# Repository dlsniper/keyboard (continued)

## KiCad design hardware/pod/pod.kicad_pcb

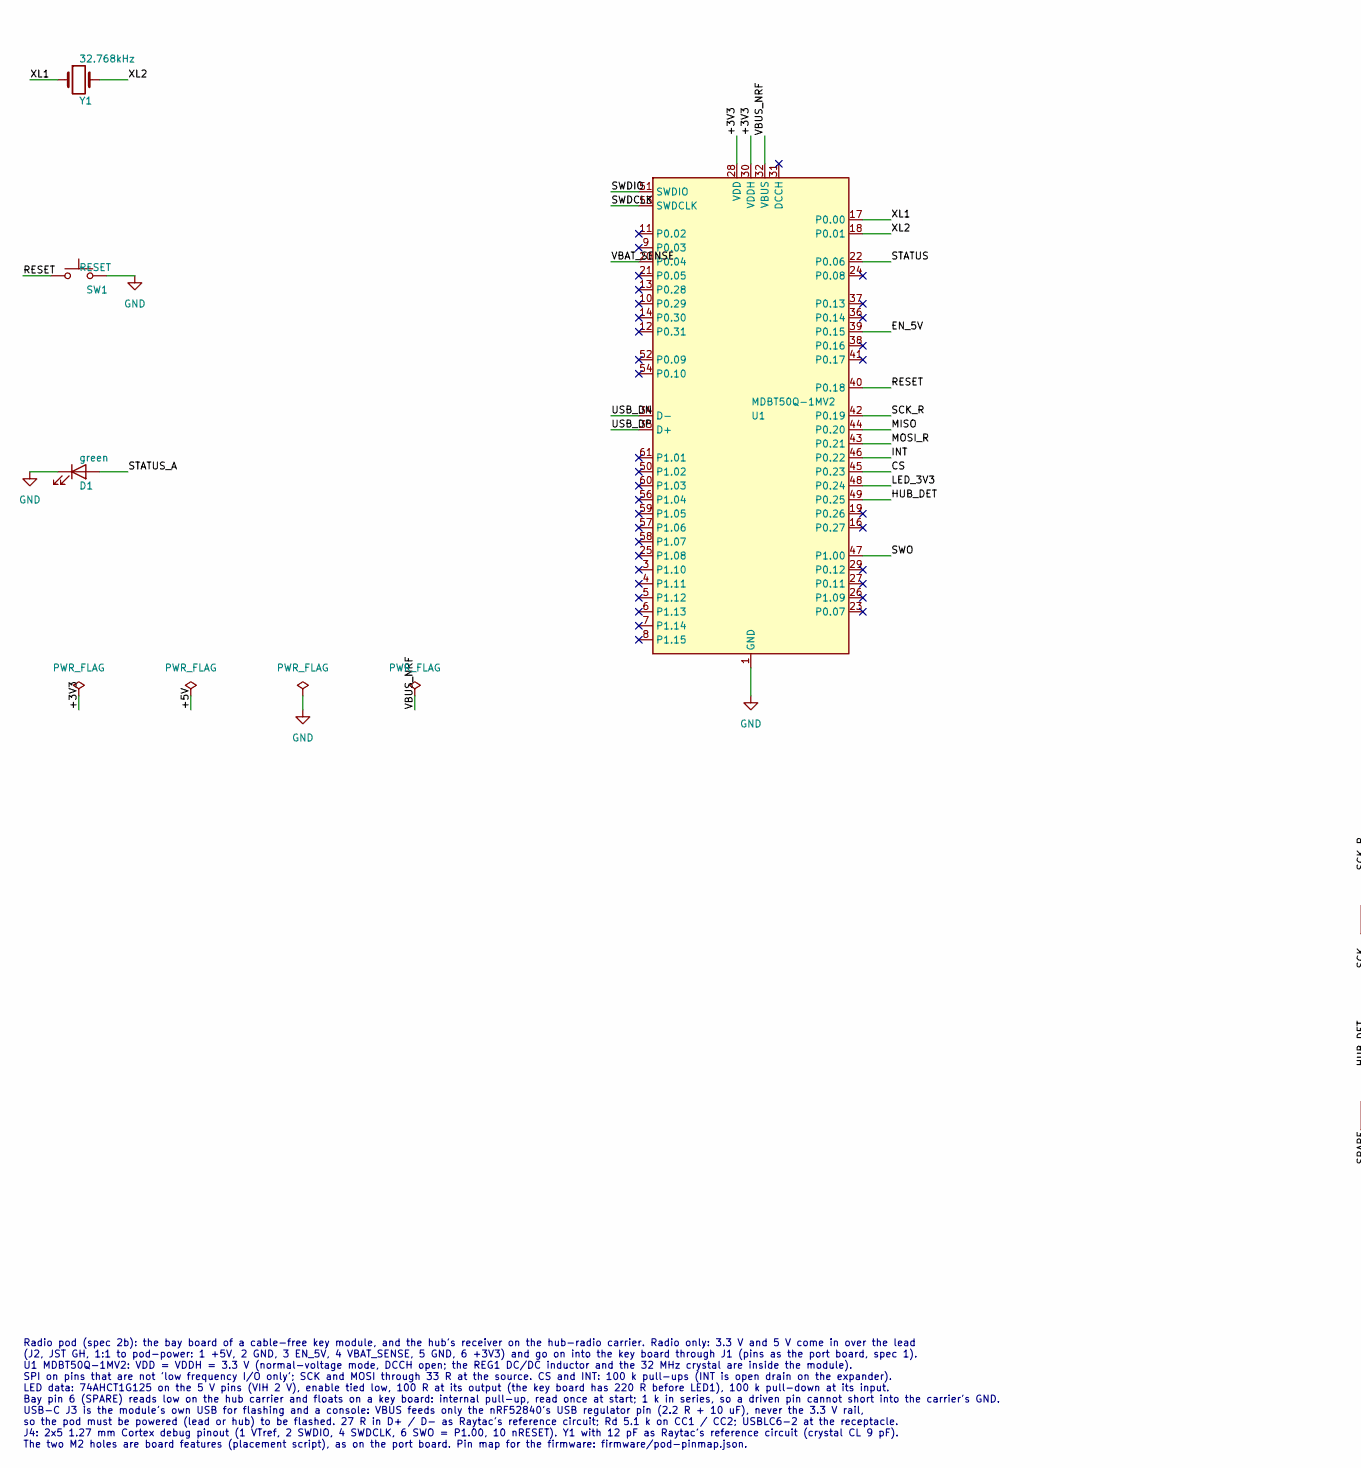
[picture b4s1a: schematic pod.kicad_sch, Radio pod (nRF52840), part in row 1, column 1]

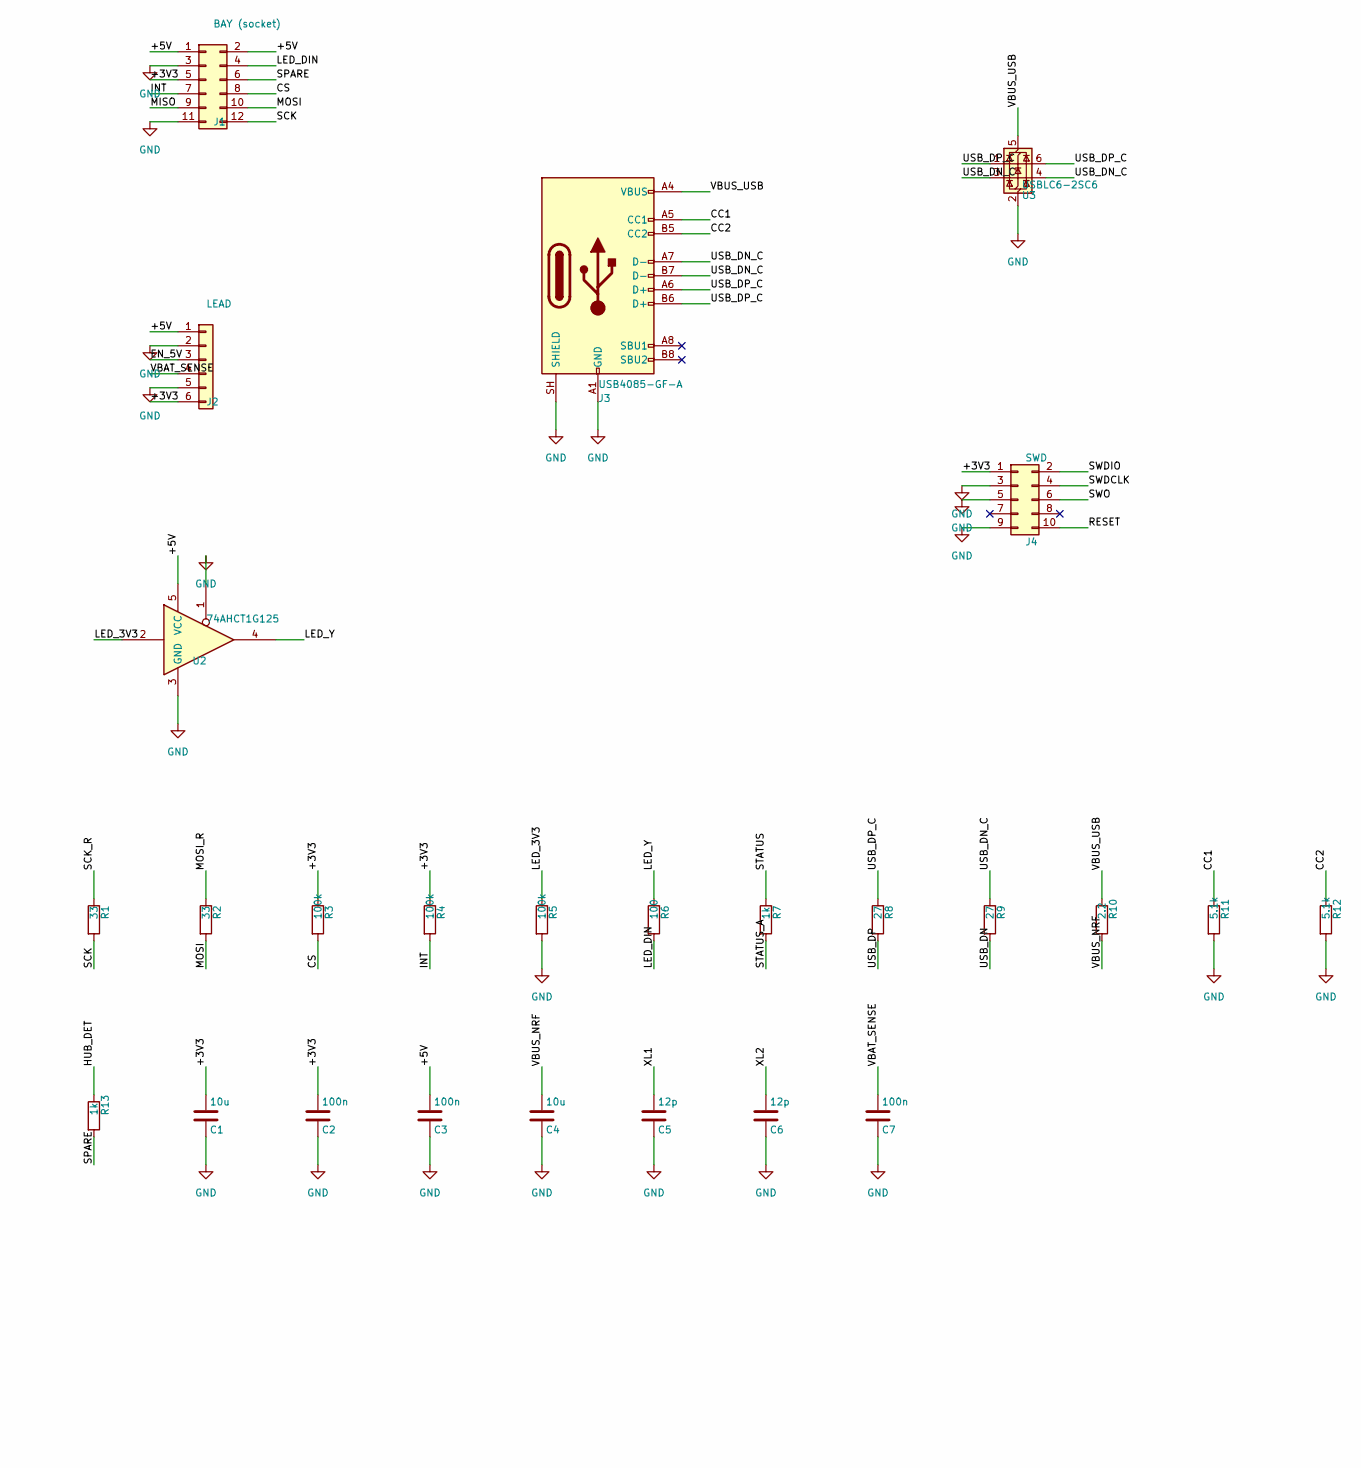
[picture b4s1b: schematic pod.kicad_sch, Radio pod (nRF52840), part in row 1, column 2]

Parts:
C1, C4: 10u; C_0805_2012Metric; Voltage 10V
C2, C3, C7: 100n; C_0603_1608Metric; Voltage 16V
C5, C6: 12p; C_0603_1608Metric; Voltage 50V
D1: green; LED_0603_1608Metric
J1: BAY (socket); PinSocket_2x06_P2.54mm_Vertical; MPN generic 2x6 2.54 mm socket
J2: LEAD; JST_GH_SM06B-GHS-TB_1x06-1MP_P1.25mm_Horizontal; MPN JST SM06B-GHS-TB
J3: USB4085-GF-A; USB_C_Receptacle_GCT_USB4085; MPN GCT USB4085-GF-A
J4: SWD; PinHeader_2x05_P1.27mm_Vertical_SMD; MPN 2x5 1.27 mm Cortex debug header (Samtec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
R1, R2: 33; R_0603_1608Metric; Tolerance 1%
R3, R4, R5: 100k; R_0603_1608Metric; Tolerance 1%
R6: 100; R_0603_1608Metric; Tolerance 1%
R7, R13: 1k; R_0603_1608Metric; Tolerance 1%
R8, R9: 27; R_0603_1608Metric; Tolerance 1%
R10: 2.2; R_0603_1608Metric; Tolerance 1%
R11, R12: 5.1k; R_0603_1608Metric; Tolerance 1%
SW1: RESET; SW_SPST_PTS647_Sx38; MPN C&K PTS647 class
U1: MDBT50Q-1MV2; Raytac_MDBT50Q; MPN Raytac MDBT50Q-1MV2 (nRF52840, chip ant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
U2: 74AHCT1G125; SOT-23-5; MPN TI SN74AHCT1G125DBVR
U3: USBLC6-2SC6; SOT-23-6; MPN ST USBLC6-2SC6
Y1: 32.768kHz; Crystal_SMD_3215-2Pin_3.2x1.5mm; MPN 32.768 kHz, 3215, CL 9 pF, 20 ppm (ref.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

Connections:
/+3V3: C1.1, C2.1, J1.5, J2.6, J4.1, R3.1, R4.1, U1.28 (VDD), U1.30 (VDDH)
/+5V: C3.1, J1.1, J1.2, J2.1, U2.5 (VCC)
/CC1: J3.A5 (CC1), R11.1
/CC2: J3.B5 (CC2), R12.1
/CS: J1.8, R3.2, U1.45 (P0.23)
/EN_5V: J2.3, U1.39 (P0.15)
/HUB_DET: R13.1, U1.49 (P0.25)
/INT: J1.7, R4.2, U1.46 (P0.22)
/LED_3V3: R5.1, U1.48 (P0.24), U2.2
/LED_DIN: J1.4, R6.2
/LED_Y: R6.1, U2.4
/MISO: J1.9, U1.44 (P0.20)
/MOSI: J1.10, R2.2
/MOSI_R: R2.1, U1.43 (P0.21)
/RESET: J4.10, SW1.1, U1.40 (P0.18)
/SCK: J1.12, R1.2
/SCK_R: R1.1, U1.42 (P0.19)
/SPARE: J1.6, R13.2
/STATUS: R7.1, U1.22 (P0.06)
/STATUS_A: D1.2 (A), R7.2
/SWDCLK: J4.4, U1.53 (SWDCLK)
/SWDIO: J4.2, U1.51 (SWDIO)
/SWO: J4.6, U1.47 (P1.00)
/USB_DN: R9.2, U1.34 (D-)
/USB_DN_C: J3.A7 (D-), J3.B7 (D-), R9.1, U3.3 (I/O2), U3.4 (I/O2)
/USB_DP: R8.2, U1.35 (D+)
/USB_DP_C: J3.A6 (D+), J3.B6 (D+), R8.1, U3.1 (I/O1), U3.6 (I/O1)
/VBAT_SENSE: C7.1, J2.4, U1.20 (P0.04)
/VBUS_NRF: C4.1, R10.2, U1.32 (VBUS)
/VBUS_USB: J3.A4 (VBUS), J3.A9 (VBUS), J3.B4 (VBUS), J3.B9 (VBUS), R10.1, U3.5 (VBUS)
/XL1: C5.1, U1.17 (P0.00), Y1.1
/XL2: C6.1, U1.18 (P0.01), Y1.2
GND: C1.2, C2.2, C3.2, C4.2, C5.2, C6.2, C7.2, D1.1 (K), J1.3, J1.11, J2.2, J2.5, J3.A1 (GND), J3.A12 (GND), J3.B1 (GND), J3.B12 (GND), J3.SH (SHIELD), J4.3, J4.5, J4.9, R5.2, R11.2, R12.2, SW1.2, U1.1 (GND), U1.2 (GND), U1.15 (GND), U1.33 (GND), U1.55 (GND), U2.1, U2.3 (GND), U3.2 (GND)

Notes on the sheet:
Radio pod (spec 2b): the bay board of a cable-free key module, and the hub's receiver on the hub-radio carrier. Radio only: 3.3 V and 5 V come in over the lead (J2, JST GH, 1:1 to pod-power: 1 +5V, 2 GND, 3 EN_5V, 4 VBAT_SENSE, 5 GND, 6 +3V3) and go on into the key board through J1 (pins as the por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

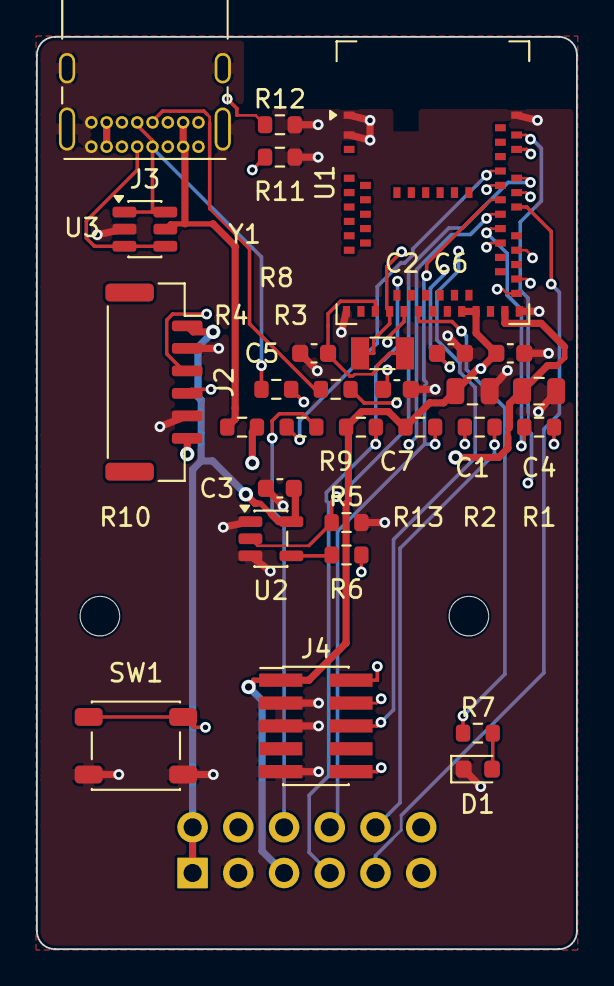
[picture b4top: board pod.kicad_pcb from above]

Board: 4 copper layers, 30.0 x 50.7 mm, 32 parts (1 on the bottom side), 33 nets.

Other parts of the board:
H1, H2: MountingHole_2.2mm_M2

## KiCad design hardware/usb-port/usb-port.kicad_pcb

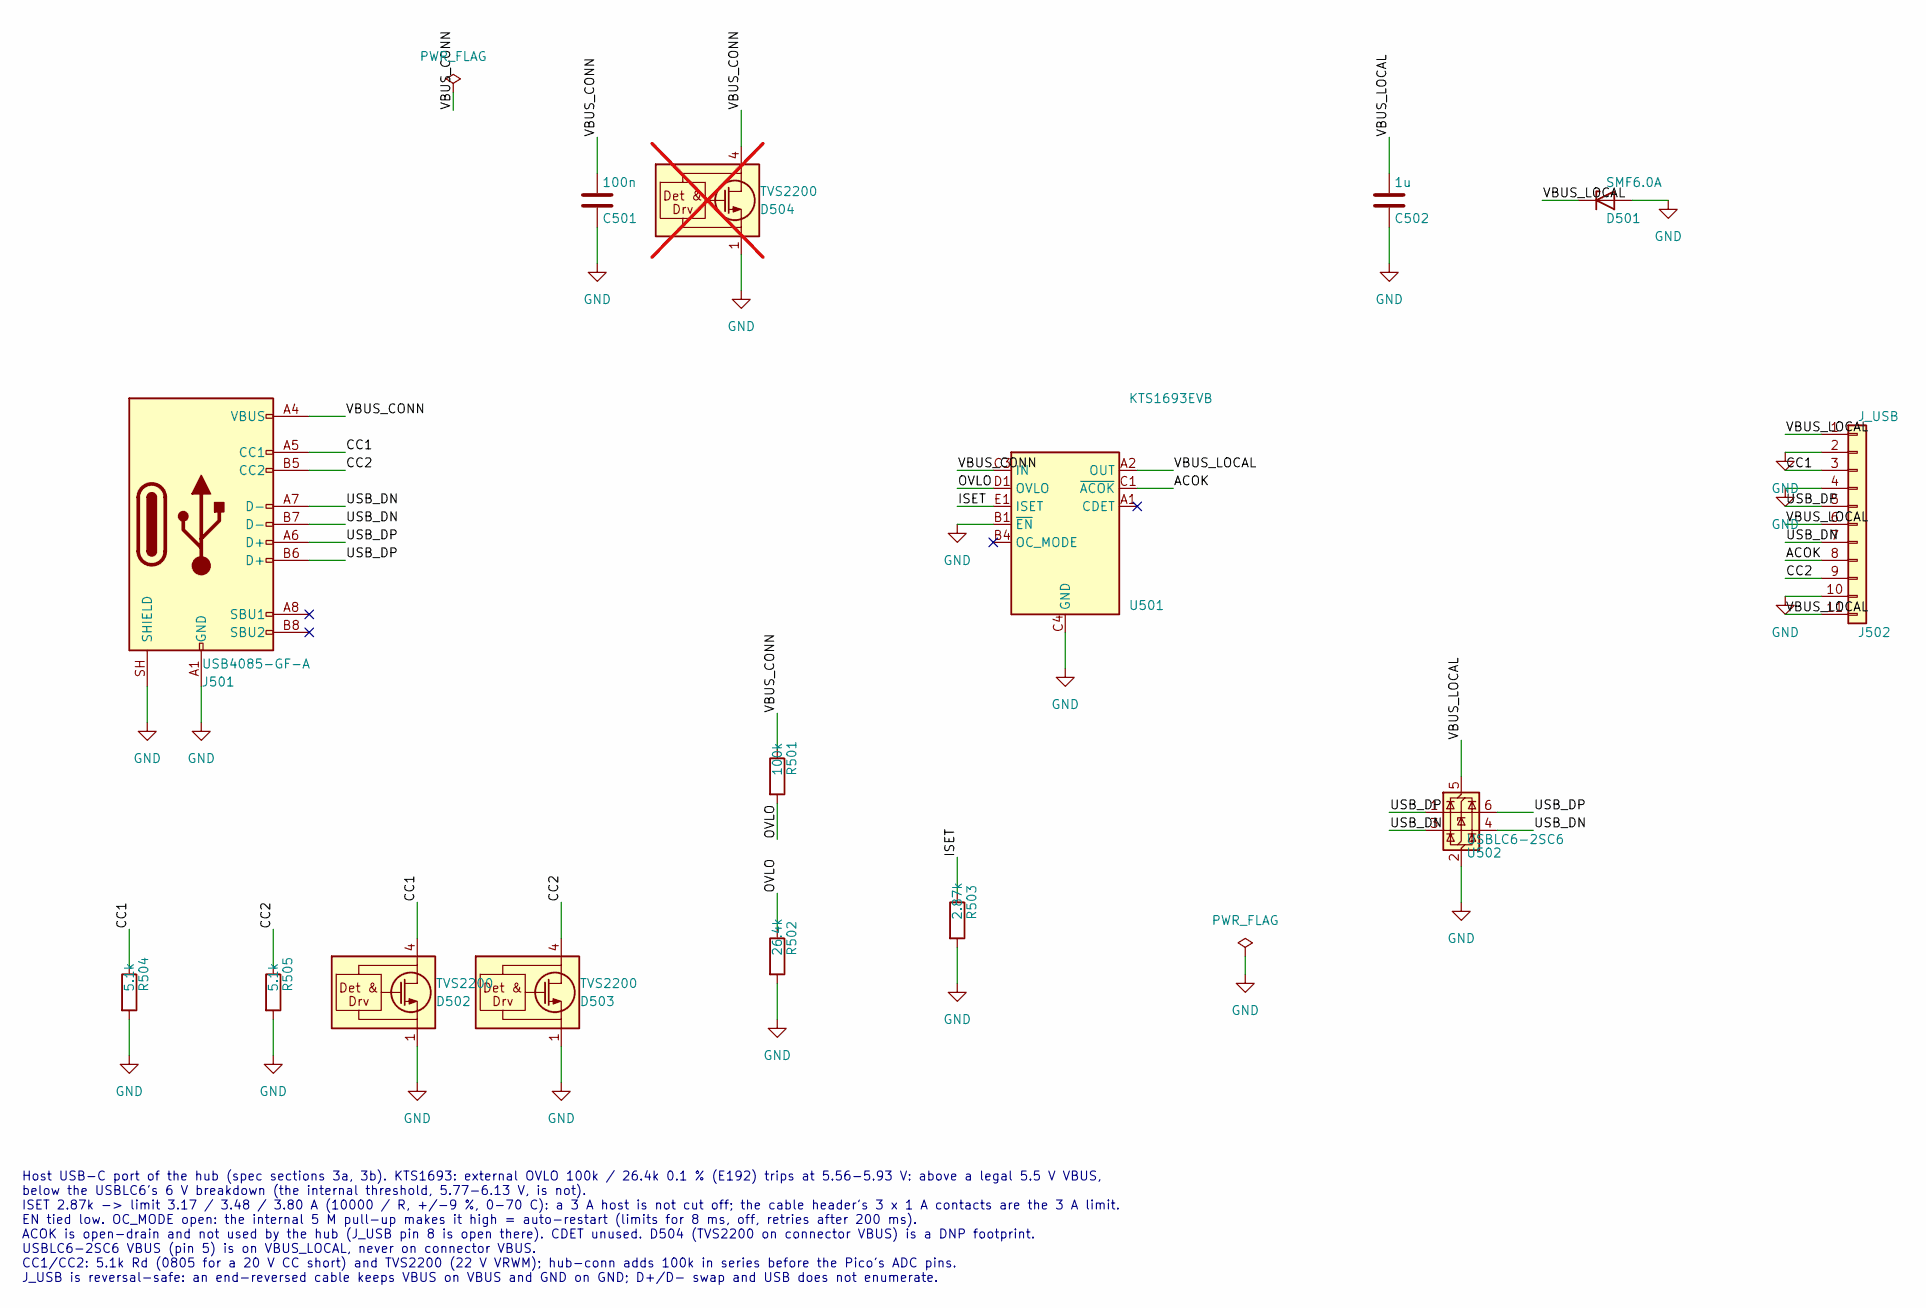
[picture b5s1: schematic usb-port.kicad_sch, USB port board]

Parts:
C501: 100n; C_0603_1608Metric; Voltage 50V
C502: 1u; C_0603_1608Metric; Voltage 25V
D501: SMF6.0A; D_SOD-123FL_Littelfuse_SMF; MPN Littelfuse SMF6.0A
D502, D503: TVS2200; TI_WSON-6-1EP_2x2mm_P0.65mm_DRV0006A_TVS2200; MPN TI TVS2200DRVR
D504: TVS2200; TI_WSON-6-1EP_2x2mm_P0.65mm_DRV0006A_TVS2200; MPN TI TVS2200DRVR; not fitted
J501: USB4085-GF-A; USB_C_Receptacle_GCT_USB4085; MPN GCT USB4085-GF-A
J502: J_USB; JST_GH_SM11B-GHS-TB_1x11-1MP_P1.25mm_Horizontal; MPN JST SM11B-GHS-TB
R501: 100k; R_0603_1608Metric; Tolerance 0.1%
R502: 26.4k; R_0603_1608Metric; Tolerance 0.1%
R503: 2.87k; R_0603_1608Metric; Tolerance 1%
R504, R505: 5.1k; R_0805_2012Metric; Tolerance 1%
U501: KTS1693EVB; Kinetic_WLCSP-20_1.935x2.16mm_Layout4x5_P0.4mm; MPN Kinetic KTS1693EVB-TR
U502: USBLC6-2SC6; SOT-23-6; MPN ST USBLC6-2SC6

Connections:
/ACOK: J502.8, U501.C1 (~ACOK)
/CC1: D502.4 (IN), D502.5 (IN), D502.6 (IN), J501.A5 (CC1), J502.3, R504.1
/CC2: D503.4 (IN), D503.5 (IN), D503.6 (IN), J501.B5 (CC2), J502.9, R505.1
/ISET: R503.1, U501.E1 (ISET)
/OVLO: R501.2, R502.1, U501.D1 (OVLO)
/USB_DN: J501.A7 (D-), J501.B7 (D-), J502.7, U502.3 (I/O2), U502.4 (I/O2)
/USB_DP: J501.A6 (D+), J501.B6 (D+), J502.5, U502.1 (I/O1), U502.6 (I/O1)
/VBUS_CONN: C501.1, D504.4 (IN), D504.5 (IN), D504.6 (IN), J501.A4 (VBUS), J501.A9 (VBUS), J501.B4 (VBUS), J501.B9 (VBUS), R501.1, U501.C3 (IN), U501.D2 (IN), U501.D3 (IN), U501.E2 (IN), U501.E3 (IN), U501.E4 (IN)
/VBUS_LOCAL: C502.1, D501.1 (K), J502.1, J502.6, J502.11, U501.A2 (OUT), U501.A3 (OUT), U501.A4 (OUT), U501.B2 (OUT), U501.B3 (OUT), U501.C2 (OUT), U502.5 (VBUS)
GND: C501.2, C502.2, D501.2 (A), D502.1 (GND), D502.2 (GND), D502.3 (GND), D502.7 (GND), D503.1 (GND), D503.2 (GND), D503.3 (GND), D503.7 (GND), D504.1 (GND), D504.2 (GND), D504.3 (GND), D504.7 (GND), J501.A1 (GND), J501.A12 (GND), J501.B1 (GND), J501.B12 (GND), J501.SH (SHIELD), J502.2, J502.4, J502.10, R502.2, R503.2, R504.2, R505.2, U501.B1 (~EN), U501.C4 (GND), U501.D4 (GND), U502.2 (GND)

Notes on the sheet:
Host USB-C port of the hub (spec sections 3a, 3b). KTS1693: external OVLO 100k / 26.4k 0.1 % (E192) trips at 5.56-5.93 V: above a legal 5.5 V VBUS, below the USBLC6's 6 V breakdown (the internal threshold, 5.77-6.13 V, is not). ISET 2.87k -> limit 3.17 / 3.48 / 3.80 A (10000 / R, +/-9 %, 0-70 C): a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

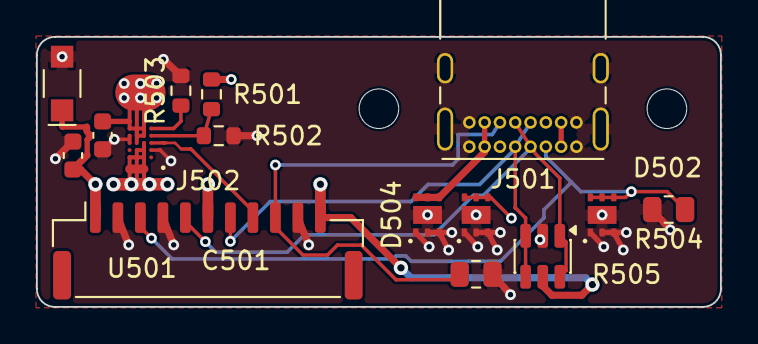
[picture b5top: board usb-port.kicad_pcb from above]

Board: 4 copper layers, 38.0 x 15.0 mm, 17 parts (0 on the bottom side), 10 nets.

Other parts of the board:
H1, H2: MountingHole_2.2mm_M2

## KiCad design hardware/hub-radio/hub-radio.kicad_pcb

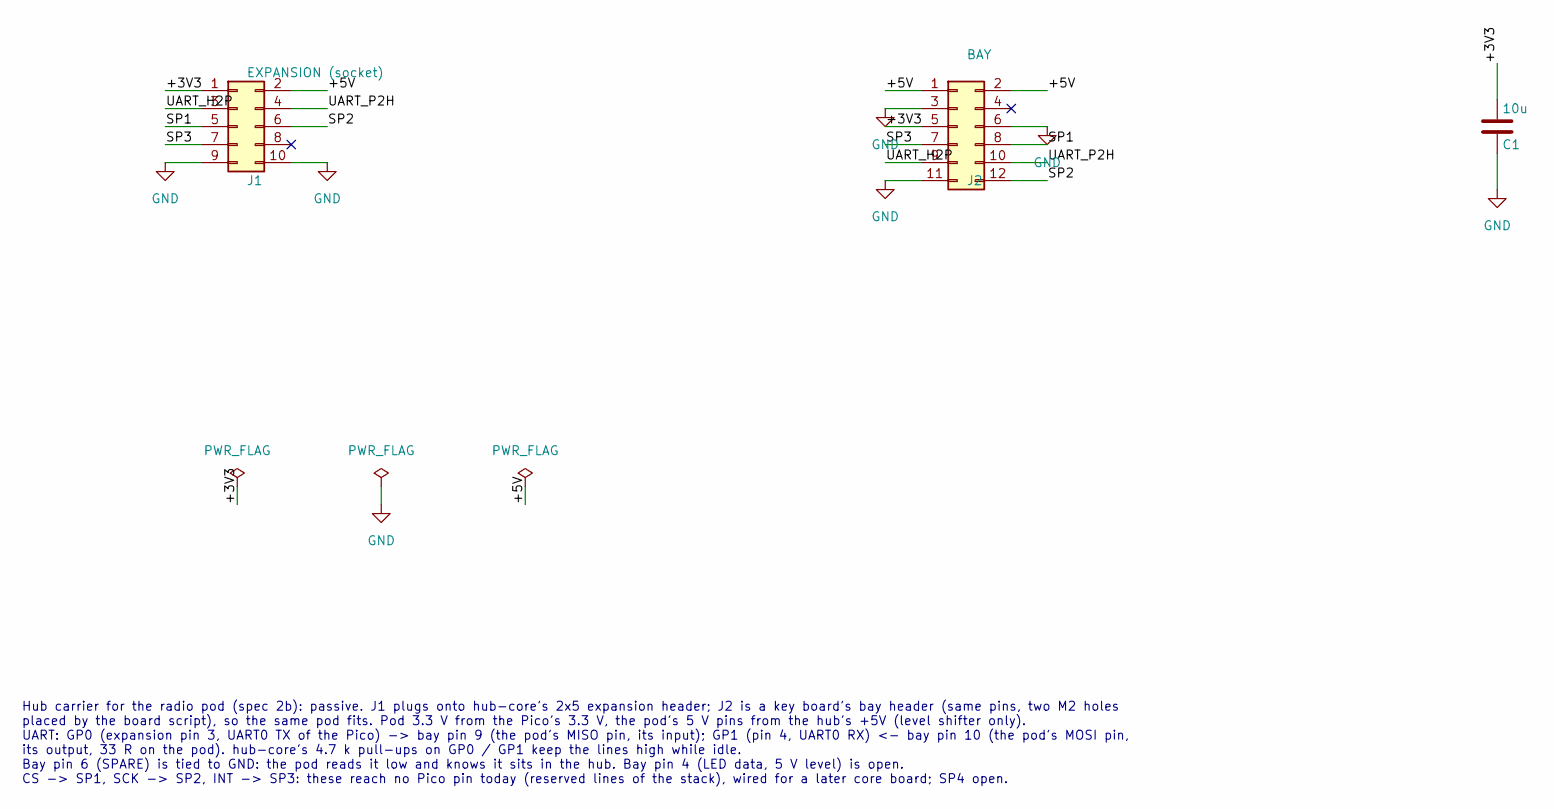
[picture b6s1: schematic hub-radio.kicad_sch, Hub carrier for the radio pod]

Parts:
C1: 10u; C_0805_2012Metric; Voltage 10V
J1: EXPANSION (socket); PinSocket_2x05_P2.54mm_Vertical; MPN generic 2x5 2.54 mm socket
J2: BAY; PinHeader_2x06_P2.54mm_Vertical; MPN generic 2x6 2.54 mm header

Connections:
/+3V3: C1.1, J1.1, J2.5
/+5V: J1.2, J2.1, J2.2
/SP1: J1.5, J2.8
/SP2: J1.6, J2.12
/SP3: J1.7, J2.7
/UART_H2P: J1.3, J2.9
/UART_P2H: J1.4, J2.10
GND: C1.2, J1.9, J1.10, J2.3, J2.6, J2.11

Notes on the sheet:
Hub carrier for the radio pod (spec 2b): passive. J1 plugs onto hub-core's 2x5 expansion header; J2 is a key board's bay header (same pins, two M2 holes placed by the board script), so the same pod fits. Pod 3.3 V from the Pico's 3.3 V, the pod's 5 V pins from the hub's +5V (level shifter only). UA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

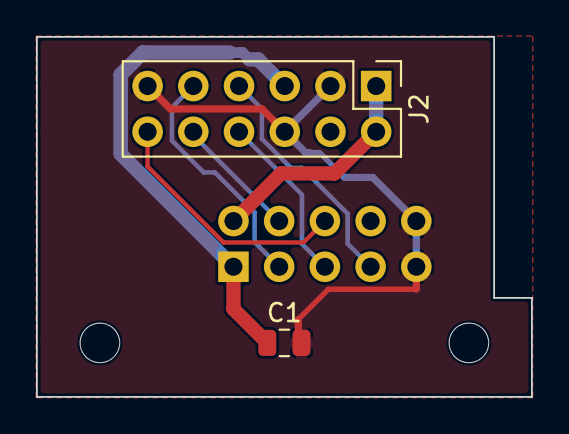
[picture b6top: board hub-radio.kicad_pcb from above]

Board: 2 copper layers, 27.5 x 20.0 mm, 5 parts (1 on the bottom side), 8 nets.

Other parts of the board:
H1, H2: MountingHole_2.2mm_M2

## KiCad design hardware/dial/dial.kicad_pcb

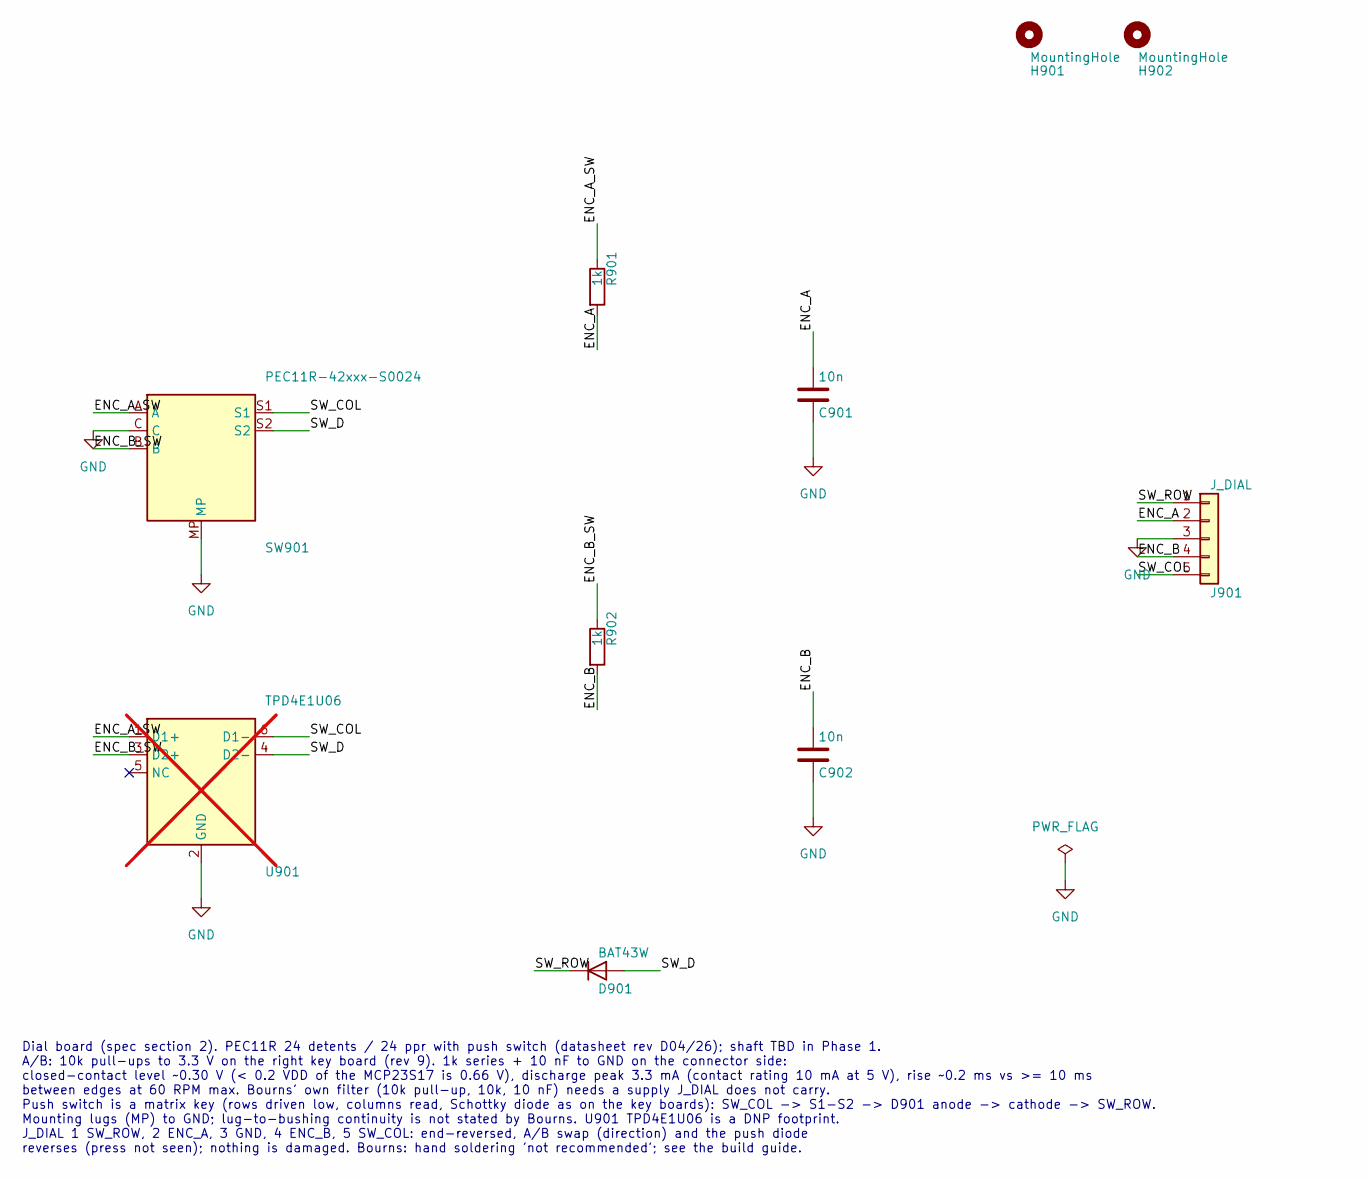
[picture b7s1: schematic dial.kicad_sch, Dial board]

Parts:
C901, C902: 10n; C_0805_2012Metric_Pad1.18x1.45mm_HandSolder; Voltage 50V
D901: BAT43W; D_SOD-123; MPN Schottky, SOD-123: BAT43W (VF 0.33 V ma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
H901, H902: MountingHole; MountingHole_2.2mm_M2_ISO7380
J901: J_DIAL; JST_GH_SM05B-GHS-TB_1x05-1MP_P1.25mm_Horizontal; MPN JST SM05B-GHS-TB
R901, R902: 1k; R_0805_2012Metric_Pad1.20x1.40mm_HandSolder; Tolerance 1%
SW901: PEC11R-42xxx-S0024; RotaryEncoder_Bourns_PEC11R-4xxxF-Sxxxx_Vertical; MPN Bourns PEC11R-42xxx-S0024
U901: TPD4E1U06; TI_SOT-23-6_DBV0006A; MPN TI TPD4E1U06DBVR; not fitted

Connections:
/ENC_A: C901.1, J901.2, R901.2
/ENC_A_SW: R901.1, SW901.A, U901.1 (D1+)
/ENC_B: C902.1, J901.4, R902.2
/ENC_B_SW: R902.1, SW901.B, U901.3 (D2+)
/SW_COL: J901.5, SW901.S1, U901.6 (D1-)
/SW_D: D901.2 (A), SW901.S2, U901.4 (D2-)
/SW_ROW: D901.1 (K), J901.1
GND: C901.2, C902.2, J901.3, SW901.C, SW901.MP, U901.2 (GND)

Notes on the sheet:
Dial board (spec section 2). PEC11R 24 detents / 24 ppr with push switch (datasheet rev D04/26); shaft TBD in Phase 1. A/B: 10k pull-ups to 3.3 V on the right key board (rev 9). 1k series + 10 nF to GND on the connector side: closed-contact level ~0.30 V (< 0.2 VDD of the MCP23S17 is 0.66 V), disch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

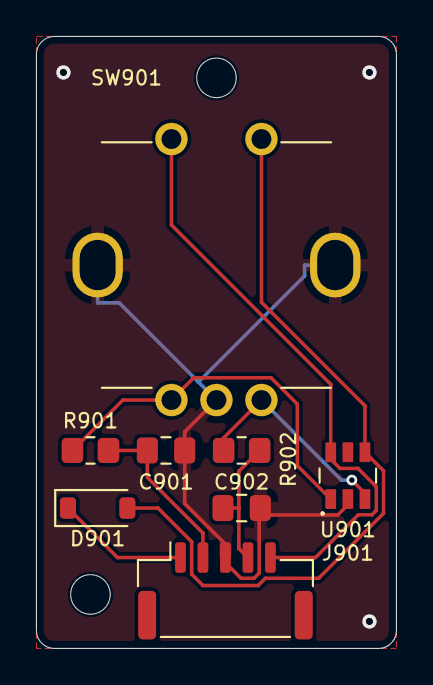
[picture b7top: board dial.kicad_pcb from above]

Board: 2 copper layers, 20.0 x 34.0 mm, 10 parts (0 on the bottom side), 8 nets.
